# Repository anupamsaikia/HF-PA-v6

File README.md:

### HF-PA-v6

RF "Lego" blocks.

The idea behind this work is to build radio-things (TM) in stages which
connect to each other.

This makes the designing, and debugging processes much easier.

- [BS170 Driver Performance](./BS170-Driver-Performance.txt)

Renderings:

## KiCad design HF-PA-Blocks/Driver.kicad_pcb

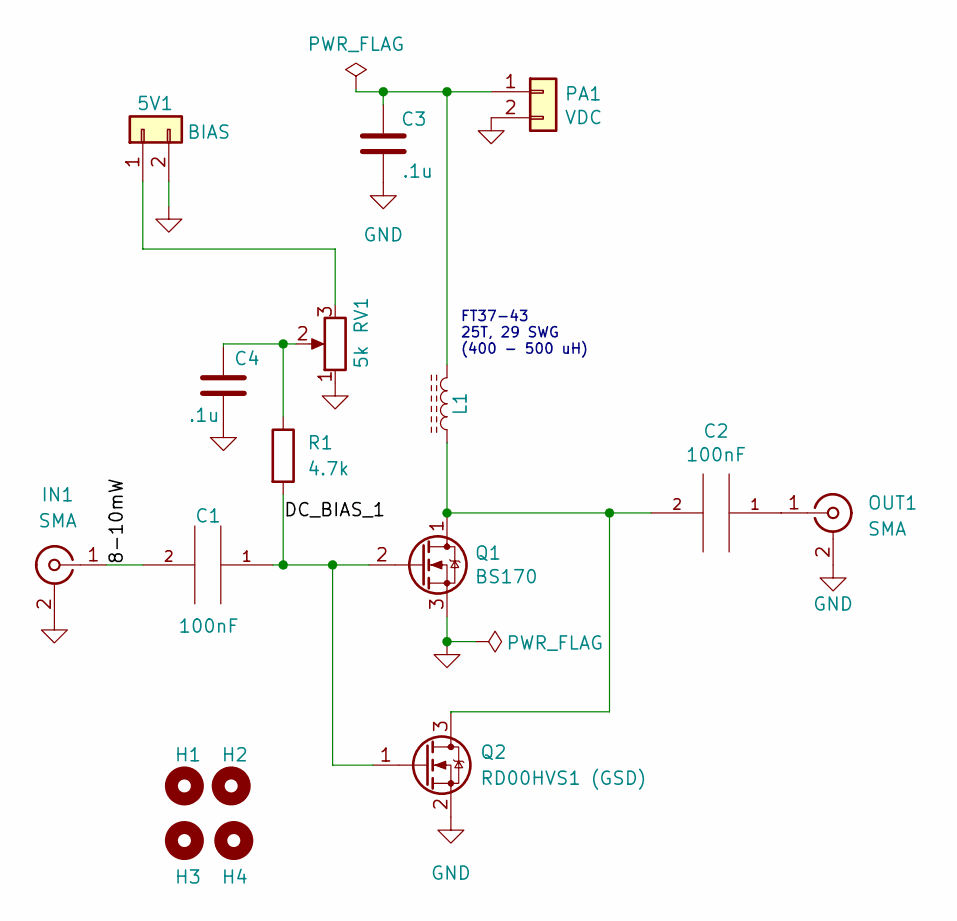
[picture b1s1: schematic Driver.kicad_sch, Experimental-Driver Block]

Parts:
5V1: BIAS; PinHeader_1x02_P2.54mm_Vertical
C1, C2: 100nF; C_1206_3216Metric_Pad1.33x1.80mm_HandSolder
C3, C4: .1u; C_1206_3216Metric_Pad1.33x1.80mm_HandSolder
H1, H2, H3, H4: MountingHole; MountingHole_2.2mm_M2
IN1: SMA; SMA_Amphenol_901-144_Vertical
L1: L_Ferrite; L_Toroid_Vertical_L10.0mm_W5.0mm_P5.08mm
OUT1: SMA; SMA_Amphenol_901-144_Vertical
PA1: VDC; PinHeader_1x02_P2.54mm_Vertical
Q1: BS170; PinSocket_1x03_P2.54mm_Vertical
Q2: RD00HVS1 (GSD); PinSocket_1x03_P2.54mm_Vertical
R1: 4.7k
RV1: 5k; Potentiometer_Runtron_RM-065_Vertical

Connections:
/8-10mW: C1.2, IN1.1 (In)
/DC_BIAS_1: C1.1, Q1.2 (G), Q2.1 (G), R1.2
GND: 5V1.2, C3.2, C4.2, IN1.2 (Ext), OUT1.2 (Ext), PA1.2, Q1.3 (S), Q2.2 (S), RV1.1
unnamed: 5V1.1, RV1.3
unnamed: C2.1, OUT1.1 (In)
unnamed: C2.2, L1.1, Q1.1 (D), Q2.3 (D)
unnamed: C3.1, L1.2, PA1.1
unnamed: C4.1, R1.1, RV1.2

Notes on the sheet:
FT37-43 25T, 29 SWG (400 - 500 uH)

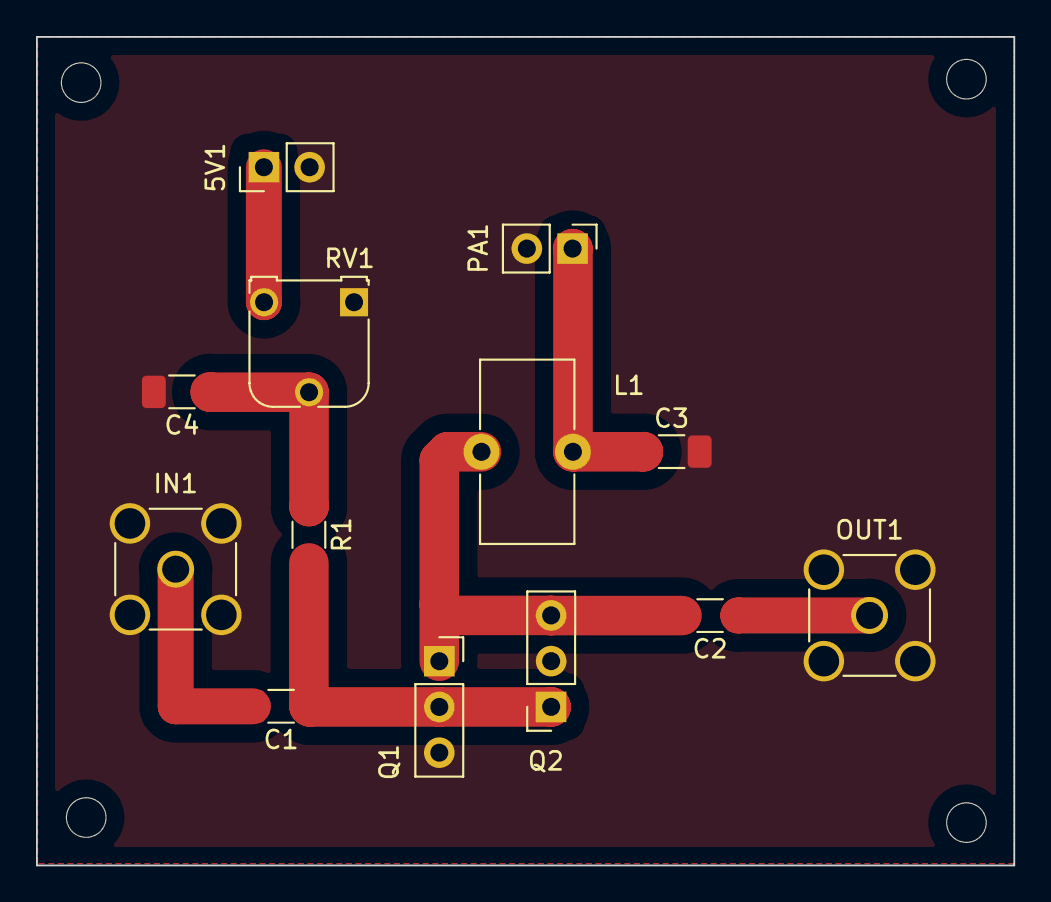
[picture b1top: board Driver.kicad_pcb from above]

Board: 2 copper layers, 54.3 x 46.0 mm, 17 parts (0 on the bottom side), 8 nets.

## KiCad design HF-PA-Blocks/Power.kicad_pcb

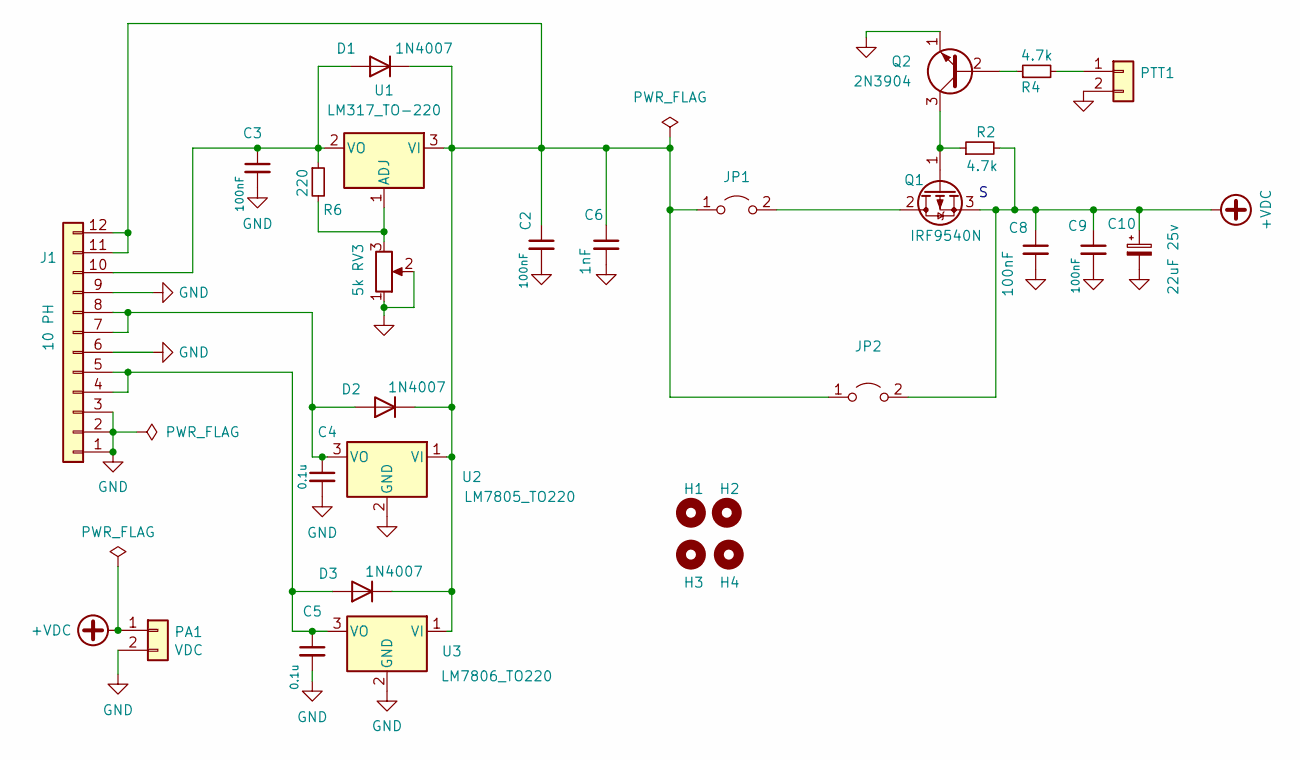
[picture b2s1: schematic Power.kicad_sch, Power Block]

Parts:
C2, C3, C8, C9: 100nF; C_1206_3216Metric_Pad1.33x1.80mm_HandSolder
C4, C5: 0.1u; C_1206_3216Metric_Pad1.33x1.80mm_HandSolder
C6: 1nF; C_1206_3216Metric_Pad1.33x1.80mm_HandSolder
C10: 22uF 25v; CP_Radial_D5.0mm_P2.50mm
D1, D2, D3: 1N4007; D_SMA_Handsoldering
H1, H2, H3, H4: MountingHole; MountingHole_2.2mm_M2
J1: 10 PH; PinHeader_1x12_P2.54mm_Vertical
JP1, JP2: Jumper_2_Open; PinHeader_1x02_P2.54mm_Vertical
PA1: VDC; PinHeader_1x02_P2.54mm_Vertical
PTT1: PTT; PinHeader_1x02_P2.54mm_Vertical
Q1: IRF9540N; TO-220-3_Vertical
Q2: 2N3904; PinSocket_1x03_P2.54mm_Vertical
R2, R4: 4.7k
R6: 220; R_1206_3216Metric_Pad1.30x1.75mm_HandSolder
RV3: 5k; Potentiometer_Runtron_RM-065_Vertical
U1: LM317_TO-220; TO-220-3_Vertical
U2: LM7805_TO220; TO-220-3_Vertical
U3: LM7806_TO220; TO-220-3_Vertical

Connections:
+VDC: C8.1, C9.1, C10.1, JP2.2 (B), PA1.1, Q1.3 (S), R2.2
GND: C2.2, C3.2, C4.2, C5.2, C6.2, C8.2, C9.2, C10.2, J1.1, J1.2, J1.3, J1.6, J1.9, PA1.2, PTT1.2, Q2.1 (E), RV3.1, RV3.2, U2.2 (GND), U3.2 (GND)
unnamed: C2.1, C6.1, D1.1 (K), D2.1 (K), D3.1 (K), J1.11, J1.12, JP1.1 (A), JP2.1 (A), U1.3 (VI), U2.1 (VI), U3.1 (VI)
unnamed: C3.1, D1.2 (A), J1.10, R6.1, U1.2 (VO)
unnamed: C4.1, D2.2 (A), J1.7, J1.8, U2.3 (VO)
unnamed: C5.1, D3.2 (A), J1.4, J1.5, U3.3 (VO)
unnamed: JP1.2 (B), Q1.2 (D)
unnamed: PTT1.1, R4.2
unnamed: Q1.1 (G), Q2.3 (C), R2.1
unnamed: Q2.2 (B), R4.1
unnamed: R6.2, RV3.3, U1.1 (ADJ)

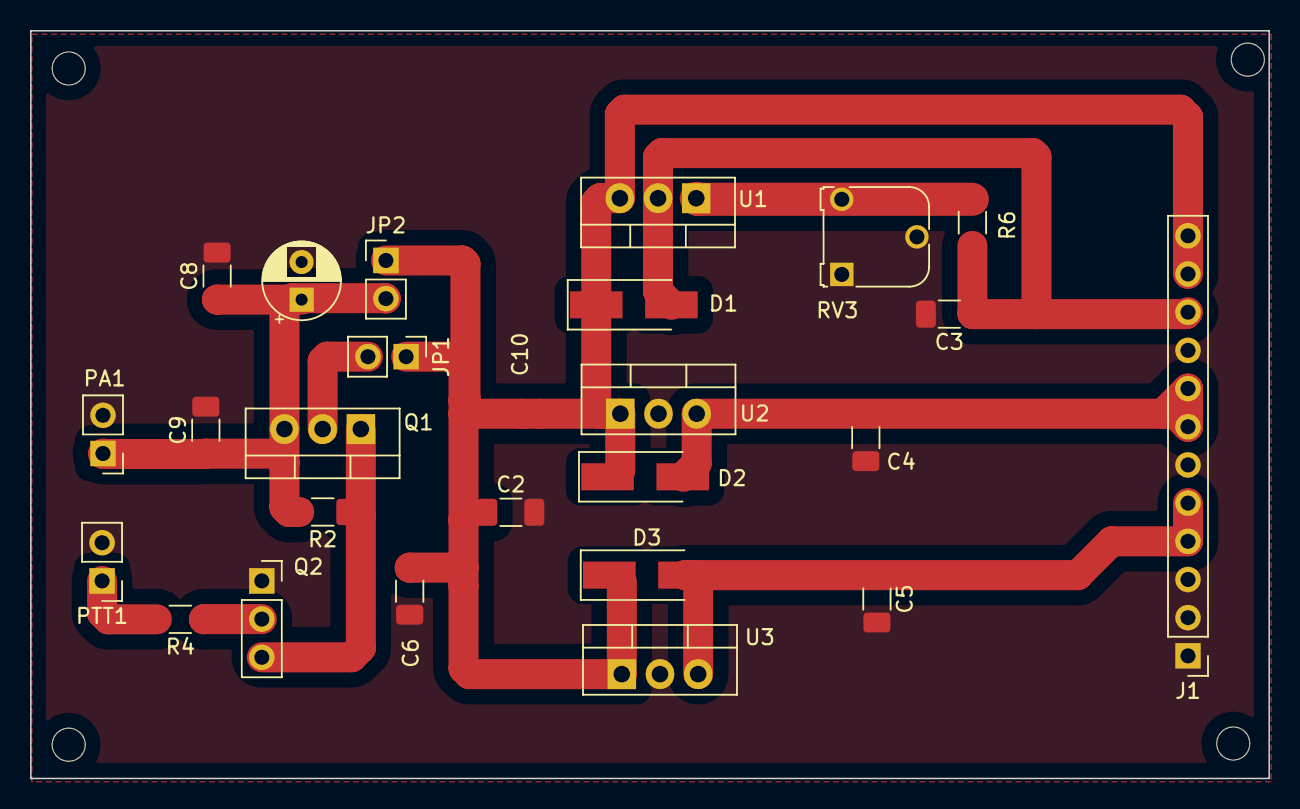
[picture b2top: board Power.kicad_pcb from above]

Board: 2 copper layers, 82.4 x 49.7 mm, 29 parts (0 on the bottom side), 11 nets.

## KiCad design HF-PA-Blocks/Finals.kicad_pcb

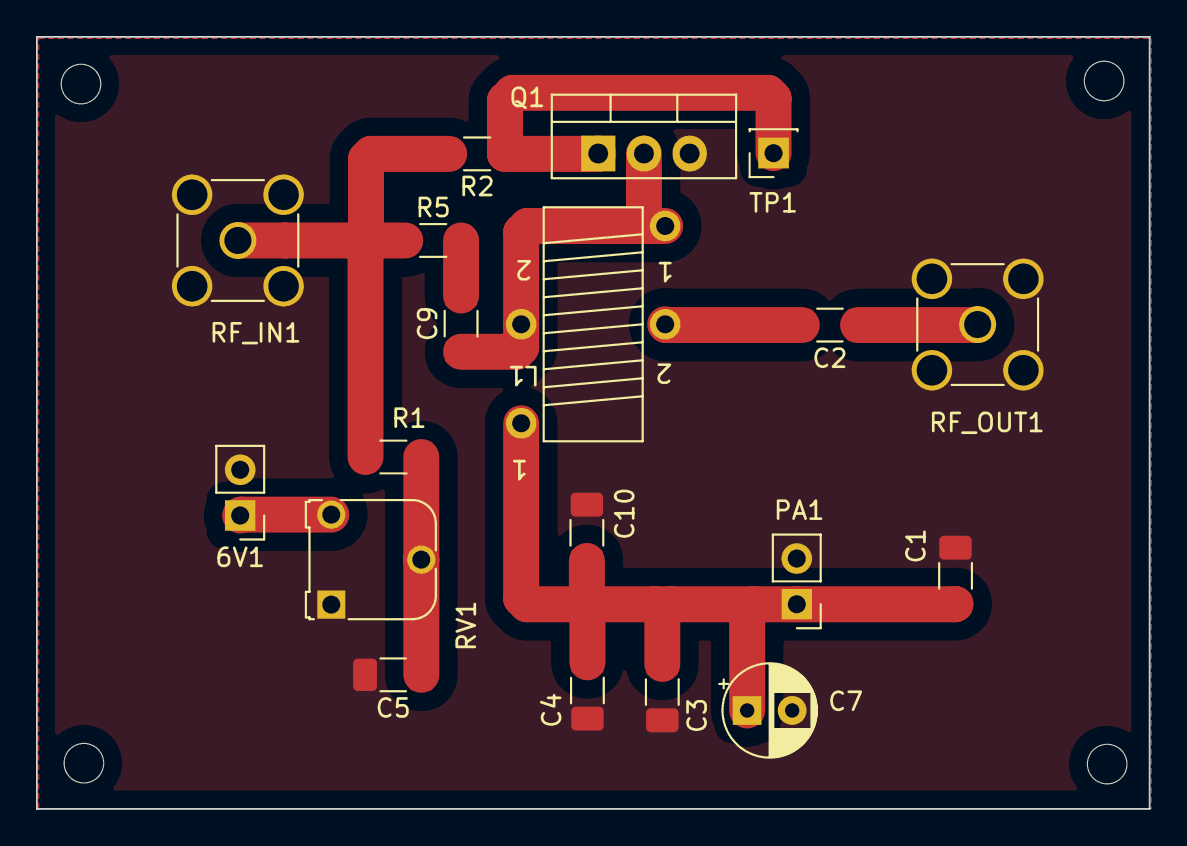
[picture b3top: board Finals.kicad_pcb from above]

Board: 2 copper layers, 61.8 x 42.9 mm, 23 parts (0 on the bottom side), 10 nets.

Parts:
6V1: BIAS; PinHeader_1x02_P2.54mm_Vertical
C1: 1nF; C_1206_3216Metric_Pad1.33x1.80mm_HandSolder
C2: 100nF (100v); C_1206_3216Metric_Pad1.33x1.80mm_HandSolder
C3, C4, C5, C10: 100nF; C_1206_3216Metric_Pad1.33x1.80mm_HandSolder
C7: 22uF 25v; CP_Radial_D5.0mm_P2.50mm
C9: 0.1u 100v; C_1206_3216Metric_Pad1.33x1.80mm_HandSolder
H1, H2, H3, H4: MountingHole; MountingHole_2.2mm_M2
L1: RFC1; FT50-43 Transformer
PA1: VDC; PinHeader_1x02_P2.54mm_Vertical
Q1: "Finals"; TO-220-3_Vertical
R1: 3.3k; R_1206_3216Metric_Pad1.30x1.75mm_HandSolder
R2: 10; R_1206_3216Metric_Pad1.30x1.75mm_HandSolder
R5: 680; R_1206_3216Metric_Pad1.30x1.75mm_HandSolder
RF_IN1: Conn_Coaxial; SMA_Amphenol_901-144_Vertical
RF_OUT1: Conn_Coaxial; SMA_Amphenol_901-144_Vertical
RV1: 5k; Potentiometer_Runtron_RM-065_Vertical
TP1: TestPoint; PinSocket_1x01_P2.54mm_Vertical

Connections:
+VDC: C1.1, C3.1, C4.1, C7.1, C10.1, L1.2, PA1.1
/DRAIN: C9.1, L1.1, L1.4, Q1.2 (D)
/RF_IN: R1.2, R2.2, R5.1, RF_IN1.1 (In)
GND: 6V1.2, C1.2, C3.2, C4.2, C5.2, C7.2, C10.2, PA1.2, Q1.3 (S), RF_IN1.2 (Ext), RF_OUT1.2 (Ext), RV1.1
unnamed: 6V1.1, RV1.3
unnamed: C2.1, RF_OUT1.1 (In)
unnamed: C2.2, L1.3
unnamed: C5.1, R1.1, RV1.2
unnamed: C9.2, R5.2
unnamed: Q1.1 (G), R2.1, TP1.1

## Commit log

2022-04-03 Initial PoC
